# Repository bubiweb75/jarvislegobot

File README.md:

<div align="center">

# JARVIS

### Assistente robotico modulare con intelligenza artificiale locale

*Repository storico: **JARVIS LEGO BOT** — piattaforma robotica evolutiva basata su ESP32-S3, elaborazione vocale locale e architettura modulare.*

**Verifica locale:** `144/144` test automatici superati (`104` Voice Bridge · `6` Firmware · `15` Robotics Platform Backend · `19` Robotics Platform Frontend + build TypeScript/Vite)

<br>

</div>

---

## Indice

- [Presentazione del Progetto](#-presentazione-del-progetto)
- [Funzionalità Attuali](#-funzionalità-attuali)
- [Architettura](#-architettura)
- [Hardware](#-hardware)
- [JARVIS Robotics Platform](#-jarvis-robotics-platform)
- [Versione Stabile (`v1.3.8-stable`)](#-versione-stabile-v138-stable)
- [Installazione e Quick Start](#-installazione-e-quick-start)
- [Documentazione](#-documentazione)
- [Roadmap](#-roadmap)
- [Licenze e Attribuzioni](#-licenze-e-attribuzioni)

---

## Presentazione del Progetto

**JARVIS** è un assistente robotico fisico da scrivania progettato per funzionare **interamente in locale** sulla rete domestica, senza dipendere da servizi cloud esterni. Nato come progetto costruttivo in mattoncini LEGO (*JARVIS LEGO BOT*), si sta evolvendo verso una piattaforma robotica modulare riutilizzabile su involucri LEGO, scocche stampate in 3D e future basi mobili.

### Come funziona
1. Il microfono `INMP441` su **ESP32-S3** acquisisce l'audio in locale a `16 kHz`: finché il robot è in `IDLE`, nessun flusso audio lascia il dispositivo e il display OLED mostra le animazioni naturali **Eyes 3.0**.
2. Quando viene pronunciata la wake word **«Hey Jarvis»** (rilevata localmente tramite `microWakeWord` INT8) oppure viene premuto il pulsante **`GPIO47`**, JARVIS passa a `LISTENING`, conserva `500 ms` di pre-roll e registra la domanda con **VAD adattivo**.
3. L'audio viene inviato via **WebSocket cifrato (`WSS` TLS)** al **Voice Bridge** su PC Windows 11, che orchestra trascrizione (`faster-whisper`), ragionamento (`Ollama`) e sintesi vocale (`Piper` Profilo 08), restituendo la risposta PCM16 all'altoparlante del robot mentre gli occhi mostrano `THINKING` e poi `SPEAKING`.

### Caratteristiche distintive
- **Privacy e controllo locale**: riconoscimento wake word on-device, zero streaming continuo in `IDLE`, STT/LLM/TTS eseguiti sulla LAN domestica.
- **Modularità hardware e software**: separazione netta tra driver I²S/I²C/RTOS su ESP32-S3, bridge vocale Python e futura piattaforma multi-identità.
- **Espandibilità progressiva**: pinout e bus predisposti per PCB carrier dedicata, contenitore 3D, sensori ambientali/prossimità e base mobile.

---

## Funzionalità Attuali

### Operative sul robot fisico + Voice Bridge (`v1.3.8-stable`)

| Funzionalità | Stato | Descrizione |
|---|---|---|
| **Wake word locale «Hey Jarvis»** | ✅ Operativa | Modello `hey_jarvis_v2_int8` (`TFLite Micro`, soglia `0.970`, inferenza `~2.92 ms` su Core 0), protezione anti-ri-trigger (`200 ms` scarto DMA + guardia `1500 ms`). |
| **Eyes 3.0 su OLED** | ✅ Operativa | Rendering non bloccante (`30 FPS`) su `SH1106 128×64` I²C con espressioni sincronizzate (`IDLE`, `LISTENING`, `THINKING`, `SPEAKING`, `ERROR`). |
| **Conversazione vocale in italiano** | ✅ Operativa | Ciclo completo bidirezionale ESP32-S3 ↔ Voice Bridge ↔ ESP32-S3 su Wi-Fi LAN. |
| **VAD adattivo** | ✅ Operativa | Stima dinamica del rumore ambientale, holdoff iniziale `300 ms` (senza troncare il pre-roll), chiusura dopo `1100 ms` di silenzio, timeout `no-speech` a `2500 ms`. |
| **Whisper STT (`faster-whisper`)** | ✅ Operativa | Trascrizione locale in italiano (`small`, `beam_size=1`) con filtro trascrizioni vuote. |
| **Ollama LLM (`qwen2.5:3b`)** | ✅ Operativa | Generazione locale delle risposte con fallback su intent locali rapidi (ora, comandi base). |
| **Piper TTS (`Profilo 08`)** | ✅ Operativa | Voce `it_IT-riccardo-x_low` con pitch shift `+5` semitoni tramite `WSOLA` (senza saturazione `tanh`) e protezione `<= 640 KB` PSRAM. |
| **Voice Bridge `WSS`** | ✅ Operativa | Server `FastAPI` + `Uvicorn` TLS su LAN con autenticazione a token dedicato (`JARVIS_ESP_DEVICE_TOKEN`). |
| **Pulsante `GPIO47` & Speaker silenzioso** | ✅ Operativa | Attivazione alternativa Push-to-Talk, interruzione/cancellazione immediata (`CANCELLED → IDLE`) e zero-flush `I2S_NUM_1` in `IDLE`. |
| **Diagnostica seriale `STAT`** | ✅ Operativa | Ispezione su richiesta di `heap`, `min_heap`, `psram`, high-water mark stack Core 0 e soglie VAD. |

### Operative su PC Windows (Control Center) — *non ancora integrate nel firmware ESP32-S3*

| Funzionalità | Stato | Ambito attuale |
|---|---|---|
| **Control Center & Simulatore Desktop** | 🖥️ Solo PC | `05-Voice-AI/jarvis_app.py` (`Start_JARVIS_Control_Center.bat`): interfaccia desktop per test, impostazioni, modalità silenziosa e simulatore OLED. |
| **Personalità C & Memoria L1–L4** | 🖥️ Solo PC | `BehaviorEngine`, `MemoryEngine` (consenso esplicito, SQLite locale) e `ConversationEngine 2.0` disponibili nella suite PC/Control Center; non ancora integrati nel flusso `Voice Bridge ↔ ESP32-S3`. |

---

## Architettura

```mermaid
flowchart LR
    subgraph ESP32["ESP32-S3-DevKitC-1 N16R8 (Firmware FASE 13.8)"]
        MIC["INMP441 I2S0<br/>16 kHz Mono"] --> RX["Core 0: AudioCapture<br/>microWakeWord + Pre-Roll 500ms + VAD"]
        BTN["Pulsante GPIO47<br/>PTT / Cancel"] --> SM["Core 1: State Machine<br/>IDLE / RECORDING / PLAYING"]
        RX -->|Wake / PCM16| SM
        SM --> EYES["Core 1: Eyes 3.0<br/>OLED SH1106 I2C (30 FPS)"]
        TX["Core 0: AudioPlayback<br/>I2S1 + Zero-Flush IDLE"] --> SPK["MAX98357A +<br/>Speaker 4Ω 3W"]
        SM -->|TTS PCM16 PSRAM| TX
    end

    subgraph PC["PC Windows 11 (LAN Locale)"]
        VB["Voice Bridge<br/>FastAPI WSS TLS :8765"]
        STT["faster-whisper<br/>(small, IT)"]
        AI["Local Intent /<br/>Ollama qwen2.5:3b"]
        TTS["Piper TTS<br/>Riccardo Profilo 08 (WSOLA)"]
        VB --> STT --> AI --> TTS --> VB
    end

    SM <==>|"WSS TLS (/ws/v1/esp32)<br/>Solo dopo Wake / PTT"| VB
```

---

## Hardware

### Componenti elettronici attivi (prototipo attuale)

| Componente | Modello / Specifica | Interfaccia / Pinout ESP32-S3 | Stato |
|---|---|---|---|
| **Microcontrollore** | `ESP32-S3-DevKitC-1 N16R8` (`16 MB` Flash, `8 MB` OPI PSRAM) | USB-CDC / Wi-Fi | ✅ Attivo e collaudato |
| **Display OLED** | OLED 1,3" `128×64` (`SH1106`, `0x3C`) | `I2C`: `SDA=GPIO41`, `SCL=GPIO42` (`400 kHz`) | ✅ Attivo e collaudato |
| **Microfono** | `INMP441` MEMS digitale | `I2S_NUM_0`: `WS=GPIO4`, `SCK=GPIO5`, `SD=GPIO6` | ✅ Attivo e collaudato |
| **Amplificatore & Audio** | `MAX98357A` + Speaker `4 Ω / 3 W` | `I2S_NUM_1`: `BCLK=GPIO15`, `LRC=GPIO16`, `DIN=GPIO7` | ✅ Attivo e collaudato |
| **Pulsante fisico** | Tattile normalmente aperto | `GPIO47` (pull-up interno, attivo LOW) | ✅ Attivo e collaudato |

### Stato dei sottosistemi fisici ed espansioni

- **Prototipo elettronico attuale**: cablaggio sperimentale su breadboard/prototipo con i 5 componenti sopra elencati, pienamente collaudato in FASE 13.7–13.8.
- **PCB Carrier Board v1** ([JARVIS_CARRIER_BOARD_V1_PRODUZIONE/](JARVIS_CARRIER_BOARD_V1_PRODUZIONE/)): progettazione KiCad, BOM e file Gerber completati; **scheda PCB già ordinata**, in attesa di consegna, assemblaggio e collaudo fisico.
- **Progettazione LEGO** ([03-Mechanical-Design/](03-Mechanical-Design/)): progettazione completa *Companion Hybrid v2* (`.mpd`/`.ldr` e istruzioni di montaggio).
- **Futuro contenitore stampato in 3D**: previsto in fase successiva alla validazione della PCB carrier v1 (non ancora progettato/stampato nella versione finale).
- **Sensori futuri**: pin e indirizzi I²C riservati nel firmware per `TTP223` (`GPIO1`), `VL53L0X` (`0x29`, `XSHUT=GPIO9`), `MPU6050` (`0x68`, `INT=GPIO10`) e `BH1750` (`0x23`); non ancora collegati né attivi nel firmware stabile.
- **Base mobile B2**: studi meccanici ed elettrici preliminari in [03-Mechanical-Design/05-Mobile-Electronics/](03-Mechanical-Design/05-Mobile-Electronics/); non ancora costruita né collaudata.

---

## JARVIS Robotics Platform

La cartella [`JARVIS-Robotics-Platform/`](JARVIS-Robotics-Platform/README.md) ospita le fondamenta di una piattaforma modulare per gestire in futuro più robot e identità personalizzabili mantenendo separati firmware, profili visivi, voci e configurazioni hardware.

- **Cosa è già implementato nel repository**:
  - `10` schemi JSON formali Draft 2020-12 (`schemas/`) e motori di validazione Python (`validators/`, `15/15` test superati).
  - Contratti API/WebSocket (`contracts/`) e profili ufficiali di esempio (`profiles/`).
  - Applicazione frontend `JARVIS Identity Studio` (`JARVIS-Robotics-Platform/frontend/`, React + TypeScript + Vite) con **simulatore interattivo Eyes 3.0** (`19/19` test `vitest` e build produzione superati).
- **Stato di integrazione**: componente in evoluzione parallela, **non ancora integrata nel robot fisico ESP32-S3** né nei servizi Voice Bridge di produzione.

---

## Versione Stabile (`v1.3.8-stable`)

- **Tag ufficiale**: [`v1.3.8-stable`](https://github.com/bubiweb75/jarvislegobot/releases/tag/v1.3.8-stable)
- **Firmware stabile**: `FASE 13.8` in [`04-Firmware/arduino-hw-test/jarvis_wifi_voice_client/`](04-Firmware/arduino-hw-test/jarvis_wifi_voice_client/README.md)
- **Precedente stabile archiviata**: `FASE 12.27` conservata in [`04-Firmware/archive/fase12_27_jarvis_wifi_voice_client/`](04-Firmware/archive/fase12_27_jarvis_wifi_voice_client/)
- **Consolidamento repository**: `FASE 14` completata (audit sicurezza, anonimizzazione documentazione, `.gitignore` e rilascio pubblico).
- **Test automatici**: **`144/144` superati** (`104` Voice Bridge + `6` Firmware + `15` Robotics Platform Backend + `19` Robotics Platform Frontend).
- **Collaudo fisico su hardware (`FASE 13.7`)**: superati tutti i checkpoint (`15` conversazioni consecutive E2E con `Ollama` + `Piper Profilo 08`, timeout `no-speech` `~2.5 s`, `GPIO47` PTT/cancel, oltre `10` minuti continui con `0` reset, `0` ri-trigger e `heap` stabile a `129.252` B).

### Limitazioni tecniche note
- **Spazio partizione `app0`**: l'immagine applicativa occupa `1.299.328` byte (`99%`) su `1.310.720` byte disponibili (`11.392` byte di margine). Eventuali future espansioni richiederanno una valutazione della strategia di partizionamento della Flash da `16 MB` o ulteriori ottimizzazioni del binario.
- **Servizi AI locali su PC**: la trascrizione (`faster-whisper`), il modello LLM (`Ollama`) e la sintesi (`Piper`) richiedono un PC sulla stessa LAN con i servizi avviati.
- **Backup Flash locali**: i dump completi da `16 MB` e le immagini binarie `app0` sono conservati esclusivamente in locale e volutamente esclusi dal repository pubblico.

---

## Installazione e Quick Start

### 1. Configurazione e avvio Voice Bridge (PC Windows 11)
```powershell
# 1. Creare l'ambiente virtuale in 05-Voice-AI (se non presente) e installare le dipendenze
# 2. Copiare il file di esempio configurazione e inserire i parametri locali
copy 05-Voice-AI\.env.example 05-Voice-AI\.env

# 3. Avviare Ollama in locale (es. qwen2.5:3b) e quindi il Voice Bridge WSS (esempio LAN)
cd 05-Voice-AI
.\.venv\Scripts\python.exe -m uvicorn voice_bridge.api:app --host 0.0.0.0 --port 8765 --ssl-certfile .local_certs\jarvis_lan_cert.pem --ssl-keyfile .local_certs\jarvis_lan_key.pem
```
Per il solo **Control Center** desktop su PC, è disponibile il launcher [`Start_JARVIS_Control_Center.bat`](Start_JARVIS_Control_Center.bat) (`05-Voice-AI\jarvis_app.py`). Dettagli completi in [`05-Voice-AI/README.md`](05-Voice-AI/README.md) e [`05-Voice-AI/voice_bridge/README.md`](05-Voice-AI/voice_bridge/README.md).

### 2. Configurazione Wi-Fi e compilazione Firmware (`ESP32-S3`)
1. Copiare [`wifi_secrets.example.h`](04-Firmware/arduino-hw-test/jarvis_wifi_voice_client/wifi_secrets.example.h) in `04-Firmware/arduino-hw-test/jarvis_wifi_voice_client/wifi_secrets.h` (escluso da Git) e impostare SSID, password, IP/porta del Voice Bridge e token dispositivo.
2. Verificare le dipendenze: core `esp32:esp32` `3.3.13`, `U8g2` (`2.36.19`), `WebSockets` (`2.7.2`) e `Chirale_TensorFLowLite-2.0.0` (in `04-Firmware/experiments/fase13-wakeword/libs`).
3. Compilare con `arduino-cli`:
```powershell
arduino-cli compile --fqbn "esp32:esp32:esp32s3:PSRAM=opi,FlashSize=16M,DebugLevel=none" `
  --libraries "04-Firmware\experiments\fase13-wakeword\libs" `
  --libraries "$env:USERPROFILE\Documents\Arduino\libraries" `
  "04-Firmware\arduino-hw-test\jarvis_wifi_voice_client"
```

### 3. Avvio simulatore `JARVIS Robotics Platform` (opzionale, sviluppo)
```powershell
cd JARVIS-Robotics-Platform\frontend
npm install
npm run dev
```
Per eseguire i test della piattaforma:
```powershell
# Backend schema/profili (da root repository)
JARVIS-Robotics-Platform\.venv\Scripts\python.exe -m unittest discover -s JARVIS-Robotics-Platform\tests -p "test_*.py"

# Frontend vitest + TypeScript build
cd JARVIS-Robotics-Platform\frontend
npm test
npm run build
```

---

## Documentazione

### Firmware, Voice AI e Rilascio Corrente
- [Firmware Stabile FASE 13.8 — README Tecnico](04-Firmware/arduino-hw-test/jarvis_wifi_voice_client/README.md)
- [Voice AI & Control Center — README](05-Voice-AI/README.md) | [Voice Bridge — README](05-Voice-AI/voice_bridge/README.md)
- [FASE 13.7 — Collaudo Consolidamento](docs/FASE_13_7_COLLAUDO_CONSOLIDAMENTO.md)
- [FASE 13.8 — Versione Stabile](docs/FASE_13_8_VERSIONE_STABILE.md)
- [FASE 14.1 — Audit Repository](docs/FASE_14_1_AUDIT_REPOSITORY.md) | [FASE 14.2 — Consolidamento](docs/FASE_14_2_CONSOLIDAMENTO_REPOSITORY.md) | [FASE 14.3 — Pubblicazione GitHub](docs/FASE_14_3_PUBBLICAZIONE_GITHUB.md)

### Hardware, PCB e Meccanica
- [Pinout Hardware Definitivo](06-Hardware-Integration/HARDWARE_PINOUT.md) | [Guida Montaggio Elettronica](06-Hardware-Integration/GUIDA_MONTAGGIO_ELETTRONICA.md)
- [PCB Carrier Board v1 — Documentazione Produzione](JARVIS_CARRIER_BOARD_V1_PRODUZIONE/README_FINAL.md) | [Mappatura GPIO PCB v1](06-Hardware-Integration/JARVIS_GPIO_MAPPING_PCB_V1.md)
- [Progettazione Meccanica LEGO Companion Hybrid v2](03-Mechanical-Design/10-Restyling-LEGO-Companion/Istruzioni_Montaggio_Companion_Hybrid_v2_Visor.md) | [Studio Base Mobile B2](03-Mechanical-Design/05-Mobile-Electronics/01_Architettura_Elettrica_B2.md)

### JARVIS Robotics Platform
- [Architettura e Specifiche RP-01 / RP-02](JARVIS-Robotics-Platform/README.md) | [Report RP-03](JARVIS-Robotics-Platform/reports/REPORT-FASE-RP03.md)

### Manuali PDF Storici (`docs/manuals/`)
> *Nota: i 6 manuali illustrati in `docs/manuals/` risalgono alle fasi precedenti all'integrazione Wi-Fi/wake word (`FASE 13.8`) e descrivono l'architettura storica/generale del progetto.*
- [01 Presentazione Generale](docs/manuals/01_Presentazione_Generale_JARVIS.pdf) · [02 Elettronica e Collegamenti](docs/manuals/02_Elettronica_e_Collegamenti.pdf) · [03 Costruzione LEGO Companion v2](docs/manuals/03_Costruzione_LEGO_Companion_v2.pdf) · [04 Software Windows](docs/manuals/04_Software_e_Utilizzo_Windows.pdf) · [05 Collaudo e Manutenzione](docs/manuals/05_Collaudo_e_Manutenzione.pdf) · [06 Personalità ed Emozioni](docs/manuals/06_Personalita_Emozioni_e_Reazioni.pdf)

---

## Roadmap

| Fase | Ambito | Stato |
|---|---|---|
| **FASE 13.8** | Firmware stabile ESP32-S3 (`Eyes 3.0`, *«Hey Jarvis»*, `VAD`, `WSS`, `GPIO47`, `STAT`) | ✅ Completata |
| **FASE 14** | Revisione repository, sicurezza, `144/144` test, rilascio `v1.3.8-stable` su GitHub | ✅ Completata |
| **FASE 15** | Ricezione e collaudo PCB Carrier Board v1, cablaggio definitivo e contenitore stampato in 3D | 📋 Pianificata *(indicativa)* |
| **FASE 16** | Integrazione fisica sensori (`VL53L0X`, `MPU6050`, `BH1750`, `TTP223`) | 📋 Pianificata *(indicativa)* |
| **FASE 17** | Sviluppo e collaudo Base Mobile B2 | 📋 Pianificata *(indicativa)* |
| *Parallelo* | Evoluzione **JARVIS Robotics Platform** (Identity Studio, profili multi-robot, contratti) | 🔄 In sviluppo parallelo |

*Le fasi future (FASE 15–17 e sviluppi Robotics Platform) hanno valore indicativo e non costituiscono autorizzazione automatica allo sviluppo o al flash.*

---

## Licenze e Attribuzioni

Per l'elenco completo delle librerie e dei modelli di terze parti utilizzati (`microWakeWord` / `hey_jarvis` Apache-2.0, `TensorFlow Lite Micro` Apache-2.0, `arduinoWebSockets` LGPL-2.1, `U8g2` BSD-2-Clause, `faster-whisper` MIT, `Piper` MIT, `Ollama` MIT/Apache-2.0), consultare [THIRD_PARTY_NOTICES.md](THIRD_PARTY_NOTICES.md).

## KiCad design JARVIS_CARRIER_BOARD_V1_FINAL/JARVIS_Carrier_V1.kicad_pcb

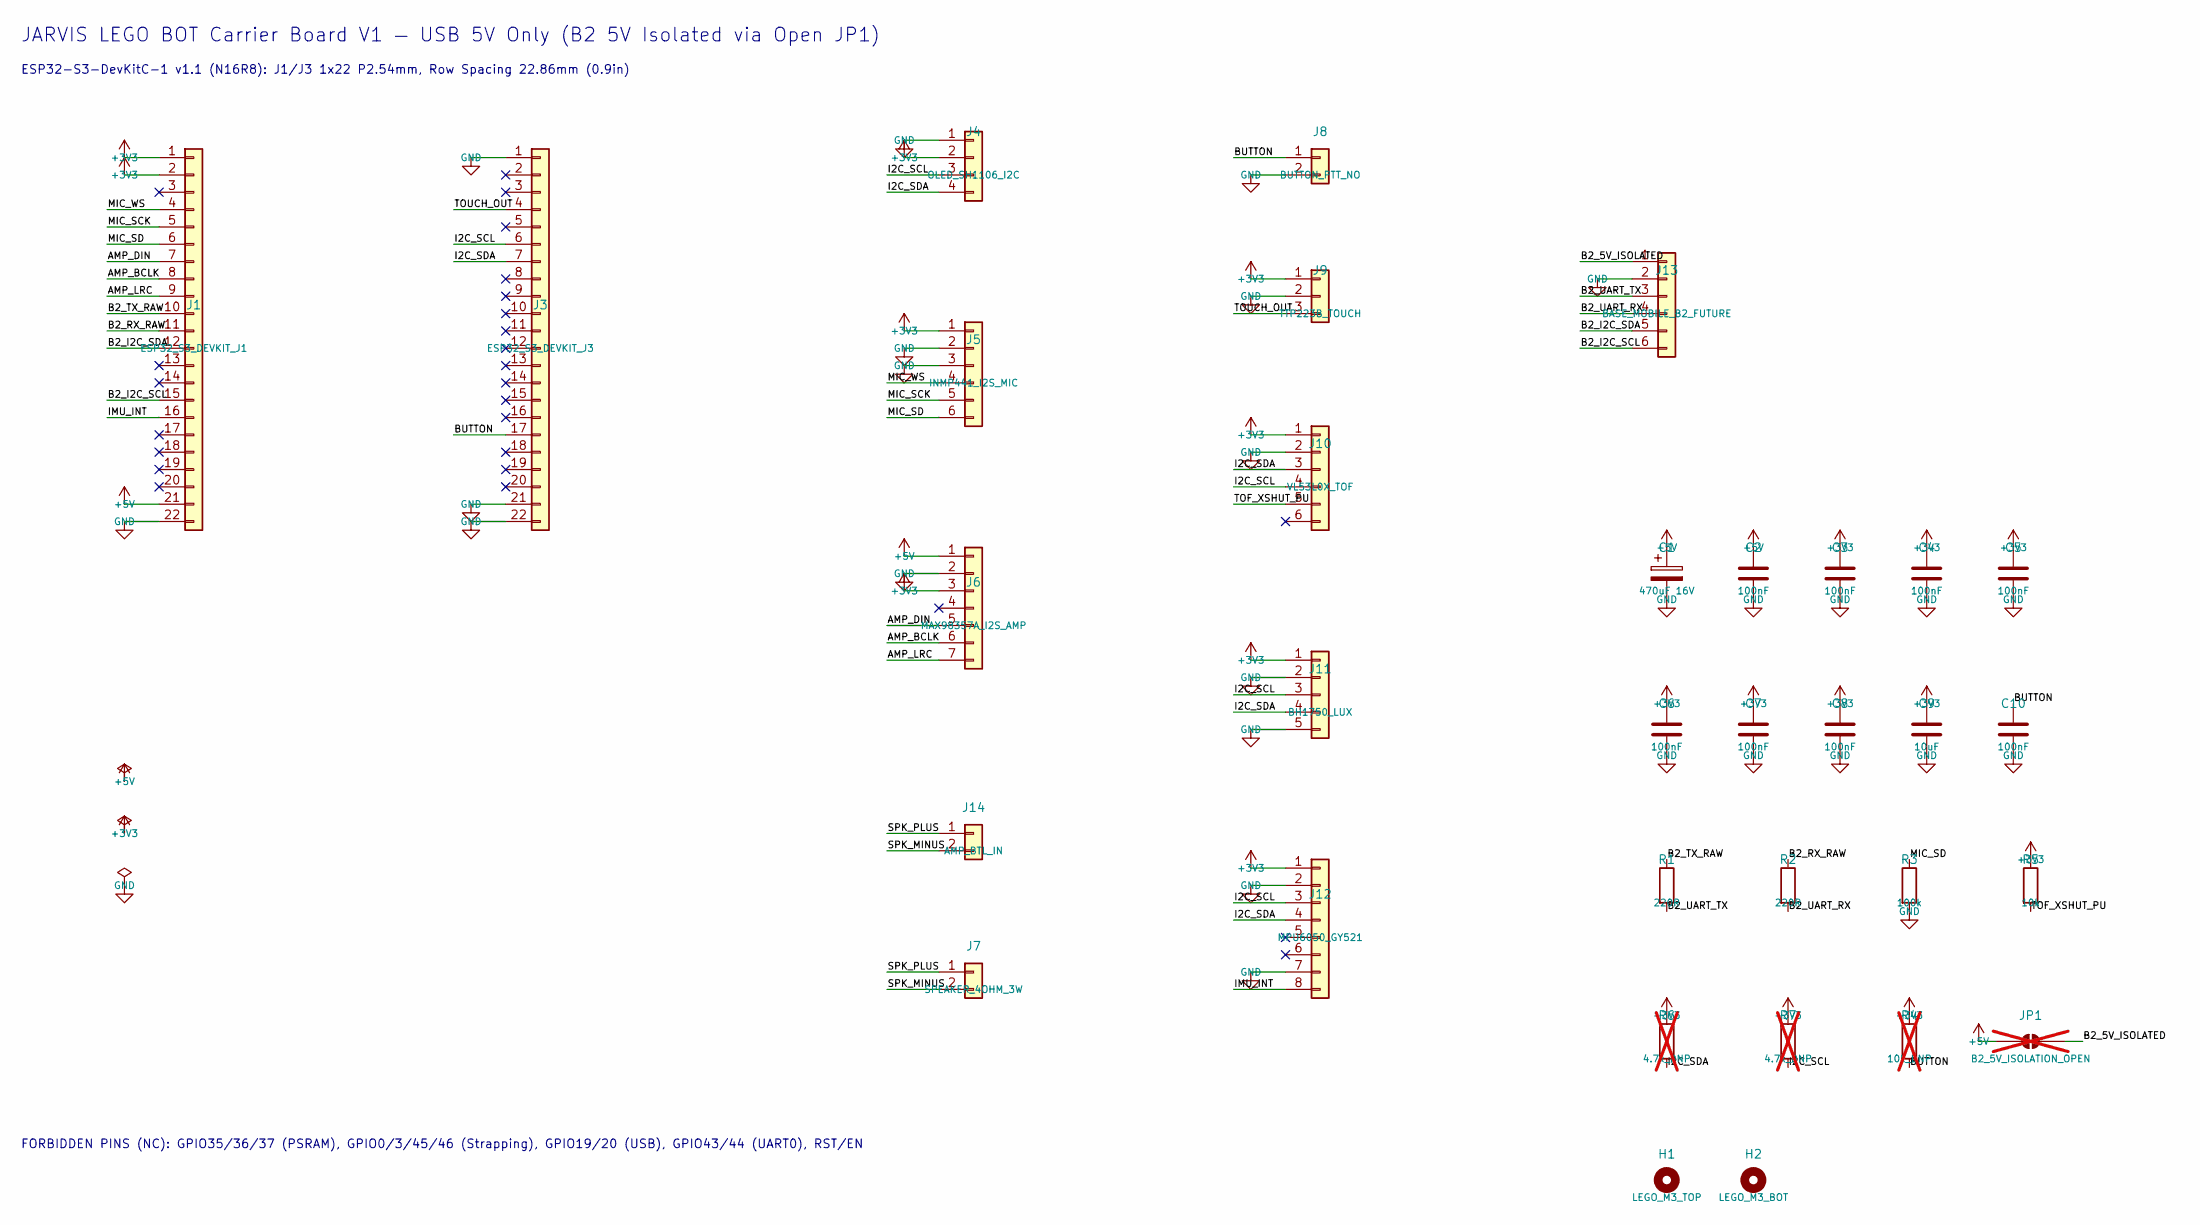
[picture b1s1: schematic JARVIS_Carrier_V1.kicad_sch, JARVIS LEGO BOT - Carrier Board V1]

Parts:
C1: 470uF 16V; CP_Radial_D8.0mm_P3.50mm
C2, C3, C4, C5, C6, C7, C8, C10: 100nF; C_0805_2012Metric
C9: 10uF; C_0805_2012Metric
H1: LEGO_M3_TOP; MountingHole_3.2mm_M3
H2: LEGO_M3_BOT; MountingHole_3.2mm_M3
J1: ESP32_S3_DEVKIT_J1; PinSocket_1x22_P2.54mm_Vertical
J3: ESP32_S3_DEVKIT_J3; PinSocket_1x22_P2.54mm_Vertical
J4: OLED_SH1106_I2C; JST_XH_B4B-XH-A_1x04_P2.50mm_Vertical
J5: INMP441_I2S_MIC; JST_XH_B6B-XH-A_1x06_P2.50mm_Vertical
J6: MAX98357A_I2S_AMP; JST_XH_B7B-XH-A_1x07_P2.50mm_Vertical
J7: SPEAKER_4OHM_3W; JST_PH_B2B-PH-K_1x02_P2.00mm_Vertical
J8: BUTTON_PTT_NO; JST_XH_B2B-XH-A_1x02_P2.50mm_Vertical
J9: TTP223B_TOUCH; JST_XH_B3B-XH-A_1x03_P2.50mm_Vertical
J10: VL53L0X_TOF; JST_XH_B6B-XH-A_1x06_P2.50mm_Vertical
J11: BH1750_LUX; JST_XH_B5B-XH-A_1x05_P2.50mm_Vertical
J12: MPU6050_GY521; JST_XH_B8B-XH-A_1x08_P2.50mm_Vertical
J13: BASE_MOBILE_B2_FUTURE; JST_XH_B6B-XH-A_1x06_P2.50mm_Vertical
J14: AMP_BTL_IN; JST_XH_B2B-XH-A_1x02_P2.50mm_Vertical
JP1: B2_5V_ISOLATION_OPEN; SolderJumper-2_P1.3mm_Open_Pad1.0x1.5mm; not fitted
R1, R2: 220R; R_0805_2012Metric
R3: 100k; R_0805_2012Metric
R4: 10k_DNP; R_0805_2012Metric; not fitted
R5: 10k; R_0805_2012Metric
R6, R7: 4.7k_DNP; R_0805_2012Metric; not fitted

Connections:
+3V3: C3.1, C4.1, C5.1, C6.1, C7.1, C8.1, C9.1, J1.1, J1.2, J4.2, J5.1, J6.3, J9.1, J10.1, J11.1, J12.1, R4.1, R5.1, R6.1, R7.1
+5V: C1.1, C2.1, J1.21, J6.1, JP1.1 (A)
/AMP_BCLK: J1.8, J6.6
/AMP_DIN: J1.7, J6.5
/AMP_LRC: J1.9, J6.7
/B2_5V_ISOLATED: J13.1, JP1.2 (B)
/B2_I2C_SCL: J1.15, J13.6
/B2_I2C_SDA: J1.12, J13.5
/B2_RX_RAW: J1.11, R2.1
/B2_TX_RAW: J1.10, R1.1
/B2_UART_RX: J13.4, R2.2
/B2_UART_TX: J13.3, R1.2
/BUTTON: C10.1, J3.17, J8.1, R4.2
/I2C_SCL: J3.6, J4.3, J10.4, J11.3, J12.3, R7.2
/I2C_SDA: J3.7, J4.4, J10.3, J11.4, J12.4, R6.2
/IMU_INT: J1.16, J12.8
/MIC_SCK: J1.5, J5.5
/MIC_SD: J1.6, J5.6, R3.1
/MIC_WS: J1.4, J5.4
/SPK_MINUS: J7.2, J14.2
/SPK_PLUS: J7.1, J14.1
/TOF_XSHUT_PU: J10.5, R5.2
/TOUCH_OUT: J3.4, J9.3
GND: C1.2, C2.2, C3.2, C4.2, C5.2, C6.2, C7.2, C8.2, C9.2, C10.2, J1.22, J3.1, J3.21, J3.22, J4.1, J5.2, J5.3, J6.2, J8.2, J9.2, J10.2, J11.2, J11.5, J12.2, J12.7, J13.2, R3.2

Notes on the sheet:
JARVIS LEGO BOT Carrier Board V1 — USB 5V Only (B2 5V Isolated via Open JP1)
ESP32-S3-DevKitC-1 v1.1 (N16R8): J1/J3 1x22 P2.54mm, Row Spacing 22.86mm (0.9in)
FORBIDDEN PINS (NC): GPIO35/36/37 (PSRAM), GPIO0/3/45/46 (Strapping), GPIO19/20 (USB), GPIO43/44 (UART0), RST/EN

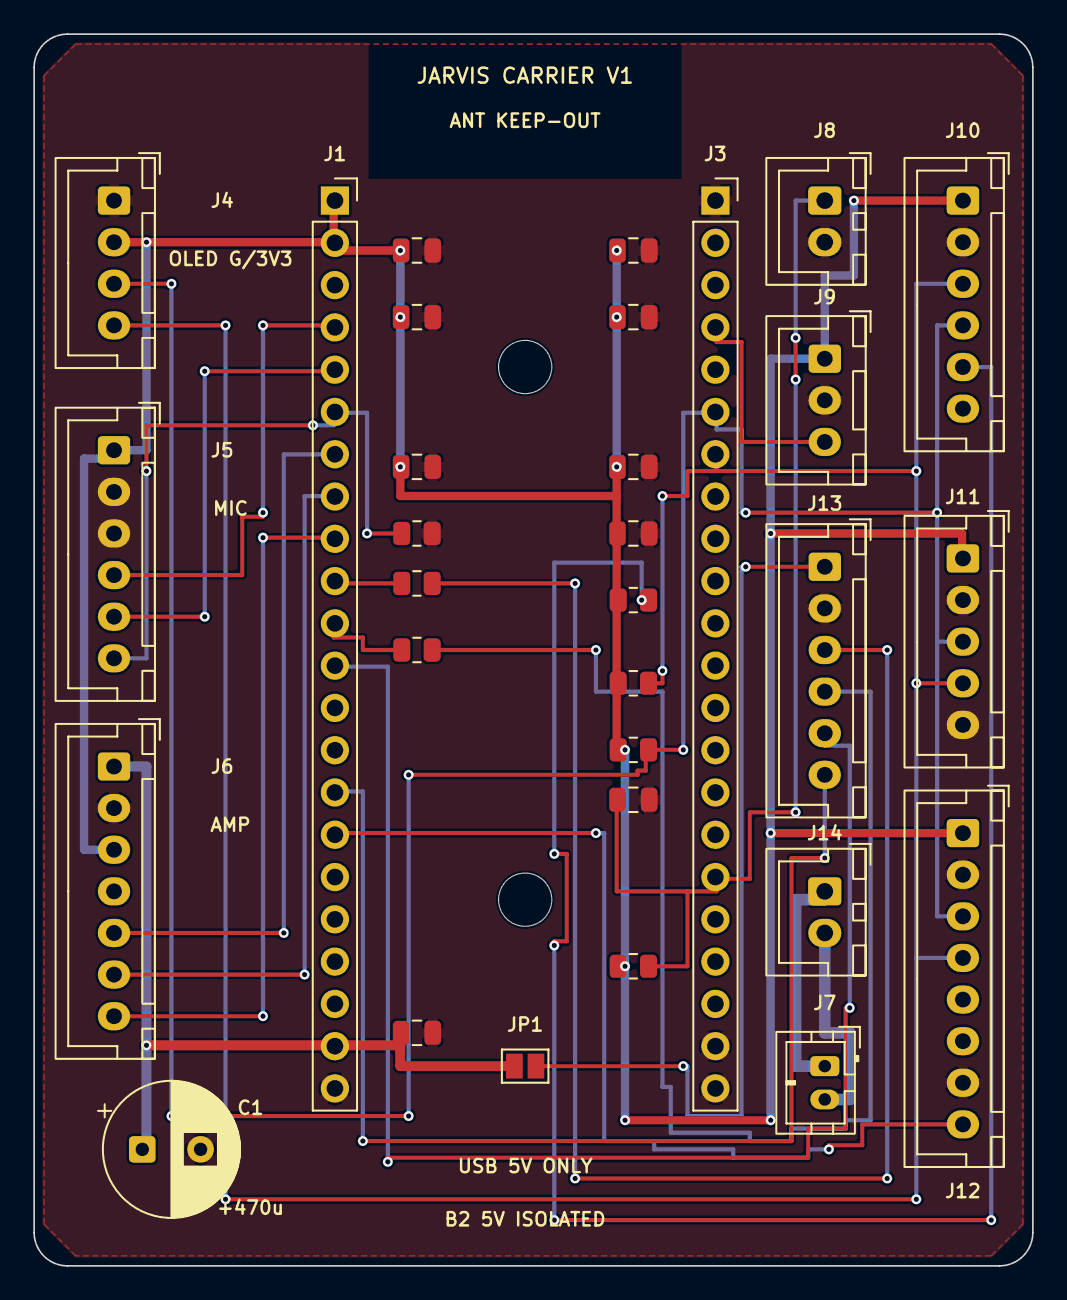
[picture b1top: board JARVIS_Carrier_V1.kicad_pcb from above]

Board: 2 copper layers, 60.0 x 74.0 mm, 33 parts (0 on the bottom side), 24 nets.

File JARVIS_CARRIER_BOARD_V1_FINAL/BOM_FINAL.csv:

"Refs","Value","Footprint","Qty","DNP"
"C1","470uF 16V","Capacitor_THT:CP_Radial_D8.0mm_P3.50mm","1",""
"C2","100nF","Capacitor_SMD:C_0805_2012Metric","1",""
"C3","100nF","Capacitor_SMD:C_0805_2012Metric","1",""
"C4","100nF","Capacitor_SMD:C_0805_2012Metric","1",""
"C5","100nF","Capacitor_SMD:C_0805_2012Metric","1",""
"C6","100nF","Capacitor_SMD:C_0805_2012Metric","1",""
"C7","100nF","Capacitor_SMD:C_0805_2012Metric","1",""
"C8","100nF","Capacitor_SMD:C_0805_2012Metric","1",""
"C9","10uF","Capacitor_SMD:C_0805_2012Metric","1",""
"C10","100nF","Capacitor_SMD:C_0805_2012Metric","1",""
"J1","ESP32_S3_DEVKIT_J1","Connector_PinSocket_2.54mm:PinSocket_1x22_P2.54mm_Vertical","1",""
"J3","ESP32_S3_DEVKIT_J3","Connector_PinSocket_2.54mm:PinSocket_1x22_P2.54mm_Vertical","1",""
"J4","OLED_SH1106_I2C","Connector_JST:JST_XH_B4B-XH-A_1x04_P2.50mm_Vertical","1",""
"J5","INMP441_I2S_MIC","Connector_JST:JST_XH_B6B-XH-A_1x06_P2.50mm_Vertical","1",""
"J6","MAX98357A_I2S_AMP","Connector_JST:JST_XH_B7B-XH-A_1x07_P2.50mm_Vertical","1",""
"J7","SPEAKER_4OHM_3W","Connector_JST:JST_PH_B2B-PH-K_1x02_P2.00mm_Vertical","1",""
"J8","BUTTON_PTT_NO","Connector_JST:JST_XH_B2B-XH-A_1x02_P2.50mm_Vertical","1",""
"J9","TTP223B_TOUCH","Connector_JST:JST_XH_B3B-XH-A_1x03_P2.50mm_Vertical","1",""
"J10","VL53L0X_TOF","Connector_JST:JST_XH_B6B-XH-A_1x06_P2.50mm_Vertical","1",""
"J11","BH1750_LUX","Connector_JST:JST_XH_B5B-XH-A_1x05_P2.50mm_Vertical","1",""
"J12","MPU6050_GY521","Connector_JST:JST_XH_B8B-XH-A_1x08_P2.50mm_Vertical","1",""
"J13","BASE_MOBILE_B2_FUTURE","Connector_JST:JST_XH_B6B-XH-A_1x06_P2.50mm_Vertical","1",""
"J14","AMP_BTL_IN","Connector_JST:JST_XH_B2B-XH-A_1x02_P2.50mm_Vertical","1",""
"R1","220R","Resistor_SMD:R_0805_2012Metric","1",""
"R2","220R","Resistor_SMD:R_0805_2012Metric","1",""
"R3","100k","Resistor_SMD:R_0805_2012Metric","1",""
"R4","10k_DNP","Resistor_SMD:R_0805_2012Metric","1","DNP"
"R5","10k","Resistor_SMD:R_0805_2012Metric","1",""
"R6","4.7k_DNP","Resistor_SMD:R_0805_2012Metric","1","DNP"
"R7","4.7k_DNP","Resistor_SMD:R_0805_2012Metric","1","DNP"
